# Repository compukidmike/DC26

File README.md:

# DEFCON 26 Projects
This is all the source code and production files for the badges we made for Defcon 26

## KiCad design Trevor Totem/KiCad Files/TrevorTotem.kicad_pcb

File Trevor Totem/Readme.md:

# Trevor Totem
The Trevor Totem was a last minute project for Defcon. It holds 7 SAOs and provides power via 2 AA batteries. It also has LEDs to light up the eyes.

If you're unfamiliar with Trevor the Roach, I suggest watching this video: https://www.youtube.com/watch?v=oOXcol_fFGQ

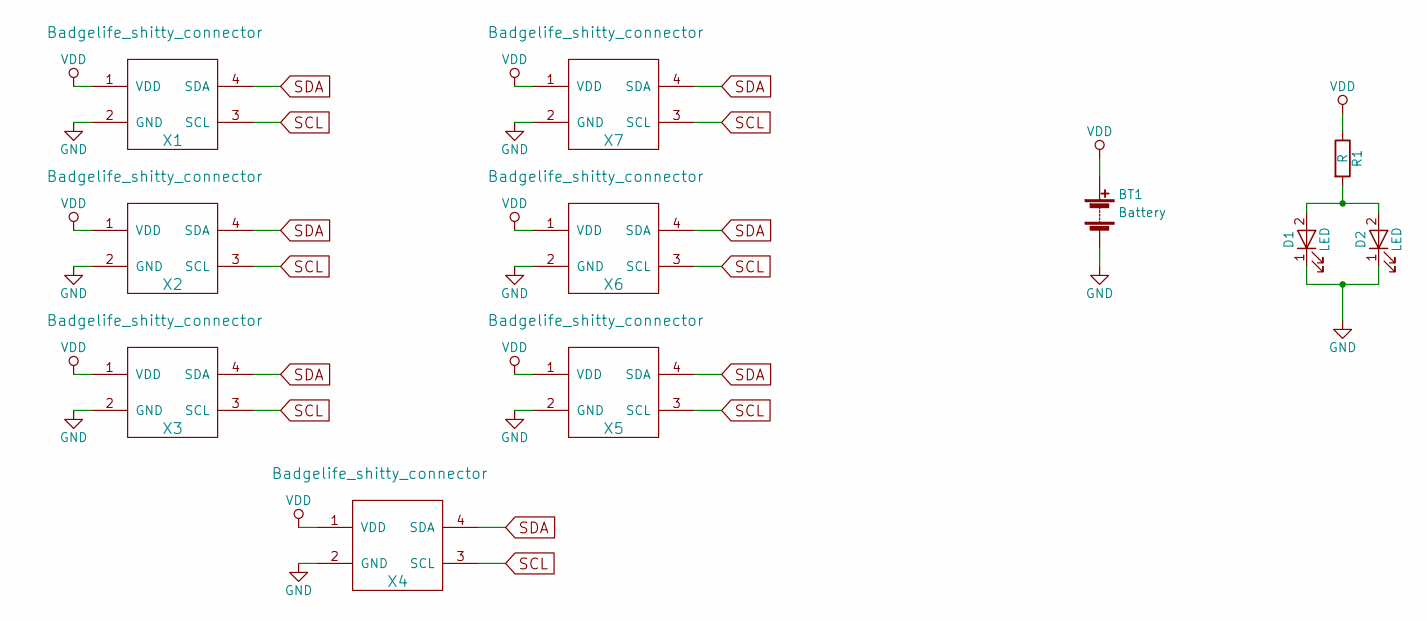
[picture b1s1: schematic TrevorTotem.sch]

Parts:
BT1: Battery; Battery-WireConn
D1, D2: LED; LED-SMD-BottomEntry-OSRAM-LS-T776
R1: R; R_0603_HandSoldering
X1, X2, X3, X4, X5, X6, X7: Badgelife_shitty_connector; Badgelife-Shitty-2x2

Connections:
GND: BT1.2 (-), D1.1 (K), D2.1 (K), X1.2 (GND), X2.2 (GND), X3.2 (GND), X4.2 (GND), X5.2 (GND), X6.2 (GND), X7.2 (GND)
unnamed: D1.2 (A), D2.2 (A), R1.2
SCL: X1.3 (SCL), X2.3 (SCL), X3.3 (SCL), X4.3 (SCL), X5.3 (SCL), X6.3 (SCL), X7.3 (SCL)
SDA: X1.4 (SDA), X2.4 (SDA), X3.4 (SDA), X4.4 (SDA), X5.4 (SDA), X6.4 (SDA), X7.4 (SDA)
VDD: BT1.1 (+), R1.1, X1.1 (VDD), X2.1 (VDD), X3.1 (VDD), X4.1 (VDD), X5.1 (VDD), X6.1 (VDD), X7.1 (VDD)

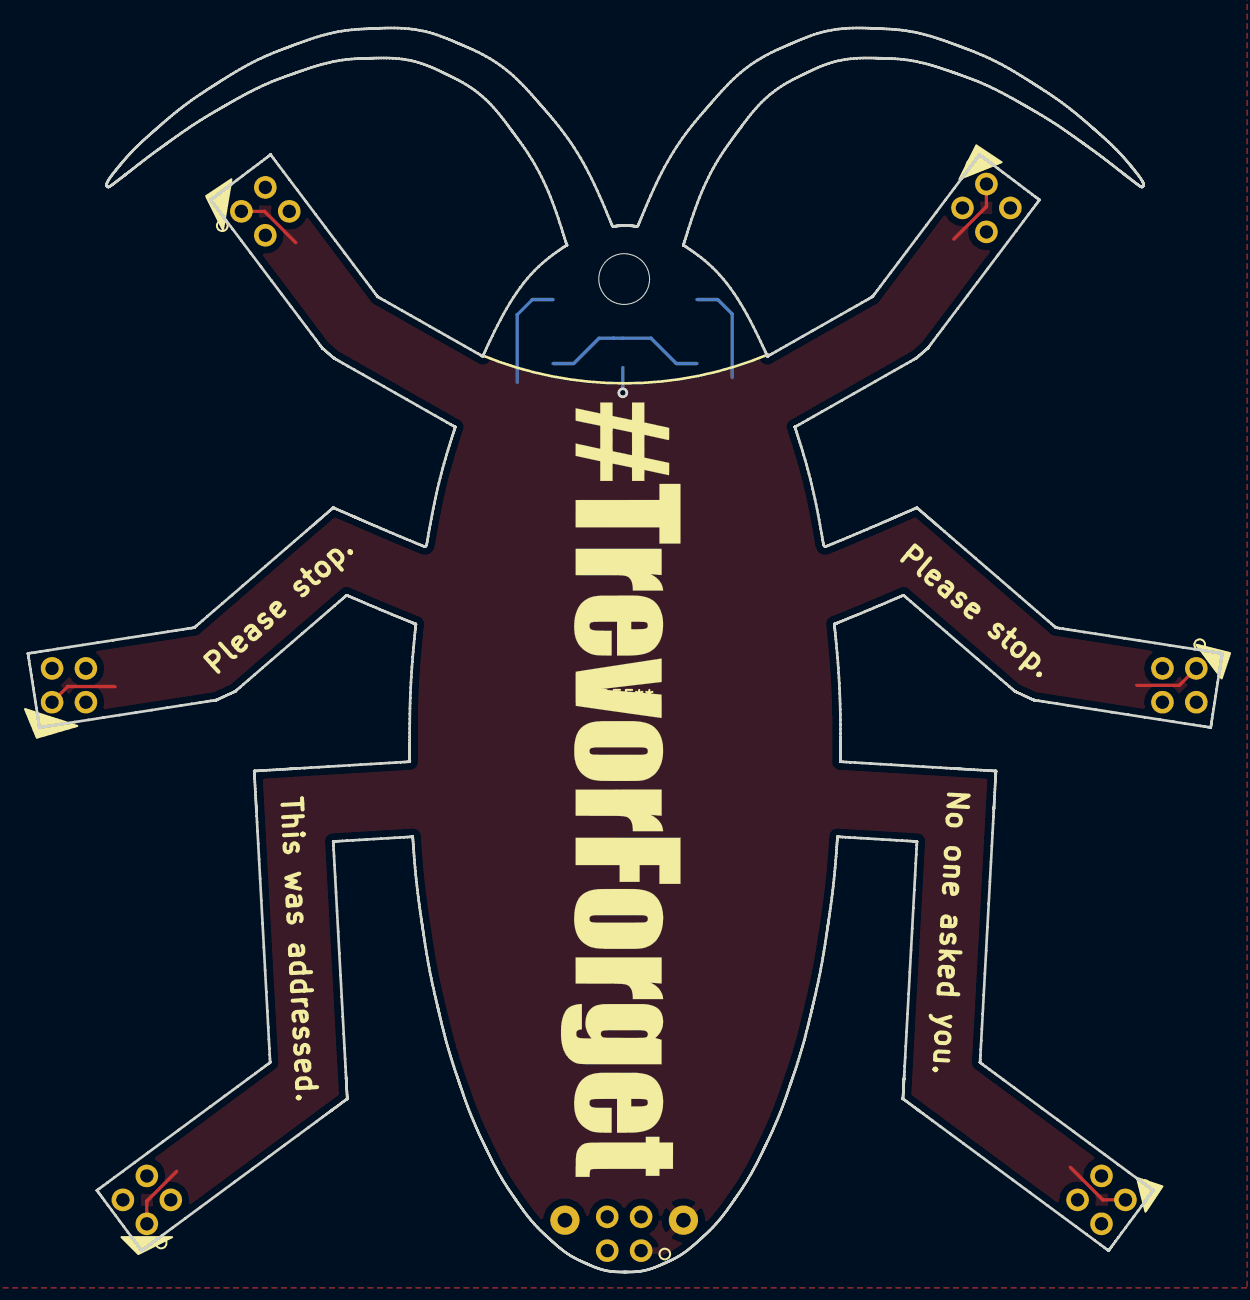
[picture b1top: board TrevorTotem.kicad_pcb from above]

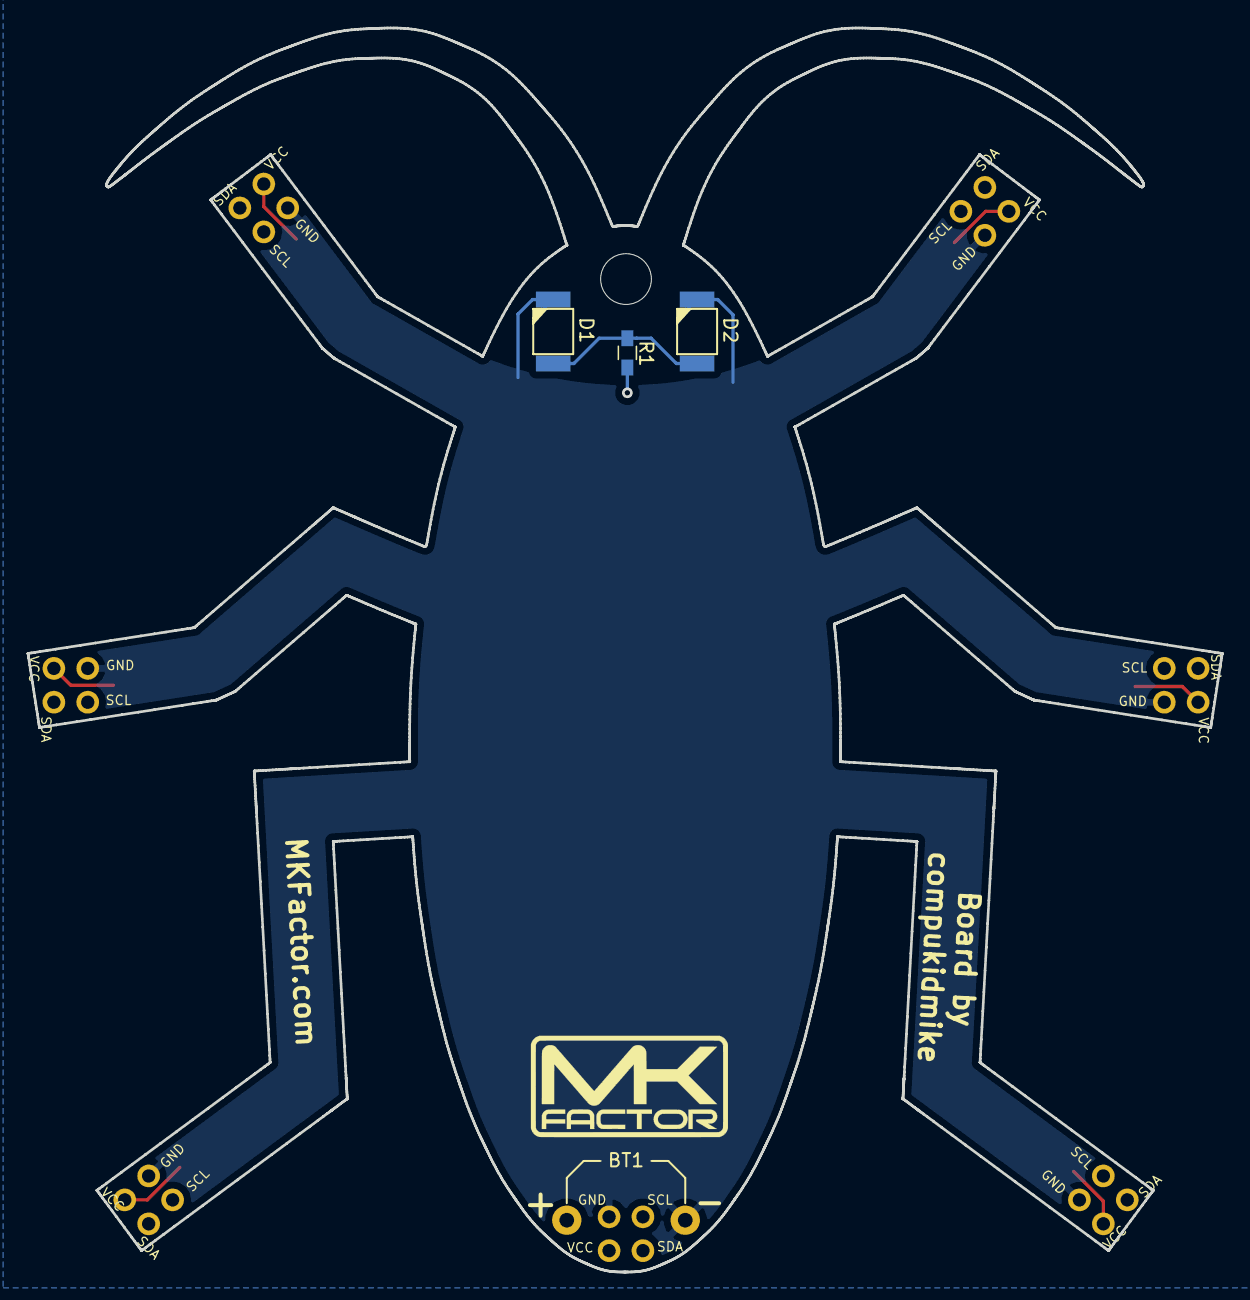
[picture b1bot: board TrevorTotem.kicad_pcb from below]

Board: 2 copper layers, 89.6 x 93.3 mm, 11 parts (4 on the bottom side), 5 nets.

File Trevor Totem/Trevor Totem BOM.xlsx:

Trevor Totem BOM
Part | Qty | Reference | Part Number | Vendor Part Number | Link | Alt Link
4 pin Header Female | 1.0 | X1, X2, X3, X4, X5, X6, X7 | PPTC022LFBN-RC | S7070-ND | https://www.digikey.com/product-detail/en/sullins-connector-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
Resistor LEDs/Transistor 0603 100 | 1.0 | R1 | RMCF0603FG100R | RMCF0603FG100RCT-ND | https://www.digikey.com/product-detail/en/yageo/RC0603JR-071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
LEDs (red) | 2.0 | D1, D2 | LS T776-P2S1-1-Z | 720-LST776-P2S1-1-Z | https://www.digikey.com/product-detail/en/osram-opto-semicon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
Battery Holder | 1.0 | BT1 | 2463.0 | 36-2463-ND | https://www.digikey.com/product-detail/en/keystone-electroni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
PCB 90x94mm | 1.0 |  |  |  | www.allpcb.com

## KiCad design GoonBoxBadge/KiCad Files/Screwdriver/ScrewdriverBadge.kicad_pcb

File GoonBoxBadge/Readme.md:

# GoonBoxBadge
  
This unofficial Defcon badge has been an amazing experience. Thank you to everyone who backed our kickstarter and to those who bought one at Defcon. The response has been amazing.

You will find everything you need to build your own badge here. If I forgot something or you need clarification on something, don't hesitate to reach out.

## Basic Badge Usage
This is the instruction sheet that was in the bag with the badge.  

The most important thing to keep in mind is to not touch the slider or the mode button when turning on the badge. When the badge is first powered on, it goes through a quick calibration of the touch buttons. If you're touching the buttons during this, the calibration will be off and the buttons won't work. If that happens, simply turn the badge off and back on.

The mode button is the top gold ring on the screwdriver, just below the coil. When pressed quickly, it will indicate the current mode on the slider LEDs. If you hold it, it will change modes. Release it when it's on the mode you want (indicated by the slider LEDs, mode 1 is the bottom LEDs). It will remember the last mode, even when turned of.

The screwdriver has 3 modes:
1. Normal mode
    * In this mode the LEDs are off until you touch the slider. The LEDs will light up according to which part of the slider you're touching. The sound will also change frequency based on slider position.
2. Bling mode
    * In this mode the LEDs are always flashing. The speed will change based on the last slider position. The speed of the GoonBox pin LED pulse will also change based on slider position.
3. TV-B-Gone mode
    * This mode is for turning off/on TVs. If you touch the lower parts of the slider, it will transmit codes as long as you're holding it. If you toucht the top of the slider, it will automatically transmit all of the TV codes without you holding it. To cancel, touch the bottom of the slider.
    * Note that the slider is slower to react in this mode. This is due to the TV code transmitting being so timing sensitive. We can't update touch data as quickly as normal during code transmission.
    * After the main badge code, we were only able to fit about half the normal TV-B-Gone codes, so some TVs won't work. However, most of the major brands should be in there.

The GoonBox pin doesn't have any modes, etc.  Simply put in a CR2032 battery and it's ready. It will react to the screwdriver, as well as normal TV remotes.

## Code
The code is very ugly, and I'm sorry for anyone that chooses to look at it. I've sprinkled some comments throughout it, hopefully it makes sense.  
There were issues with the TV-B-Gone functionality. The IR LED was put on a pin that doesn't have hardware PWM functionality. This caused many problems as the standard TV-B-Gone code wouldn't work. I made serious modificaitons to both the code and the IR codes to get it to work.  

## Lessons Learned
  * Test everything you can on the prototypes. Even if you think it might not happen, test it anyway.
  * Assembling 600 badges by hand isn't a great idea. We got it done with time to spare, but still. It's a crazy amount of work/time.
  * Pickup times/locations need to be scheduled far in advance. There were a lot of people that had a hard time finding us or were unable to get to us quickly. We'll do much better about this next year.
  
### Thank you again to everyone who made this project possible!

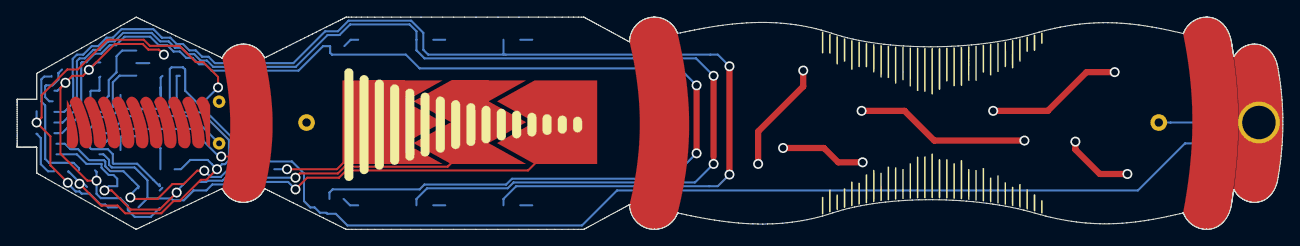
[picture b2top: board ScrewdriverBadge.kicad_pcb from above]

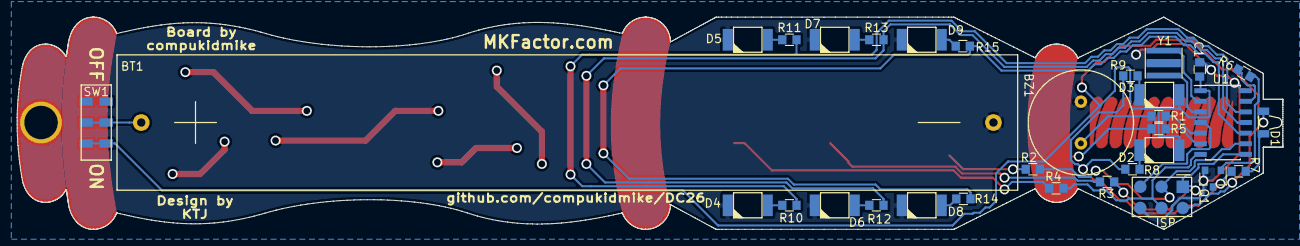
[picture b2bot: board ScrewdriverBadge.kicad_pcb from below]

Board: 2 copper layers, 151.5 x 25.4 mm, 36 parts (32 on the bottom side), 31 nets.

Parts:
BT1: Battery; Battery-2AA-BC12AAPC
BZ1: Buzzer; Buzzer-12.6mm-Murata-PKM13EPYH4000
C1: 0.1uF; R_0603_Mid
D1: LED; LED-IR-RA-OSRAM-SFH-4045N
D2, D3, D4, D5, D6, D7, D8, D9: LED; LED-SMD-BottomEntry-OSRAM-LS-T776
ISP: AVR-ISP-6; ISP-AVR-6Pin-SMD
Q1: BC817; SOT-23
R1, R2, R3, R4, R5, R6, R7, R8, R9, R10, R11, R12, R13, R14, R15: R; R_0603_Mid
SW1: SW_SPST; JS202011JCQN
TP1: SLIDER1; TestPad-SMD-1mm-Tented
TP2: SLIDER2; TestPad-SMD-1mm-Tented
TP3: SLIDER3; TestPad-SMD-1mm-Tented
TP4: FUNC; TestPad-SMD-1mm-Tented
U1: ATTINY84A-SSU; SOIC-14_3.9x8.7mm_Pitch1.27mm
Y1: Resonator; Resonator-AWSCR-3.7x3.1mm

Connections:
+BATT: C1.1, D1.2, D2.2, D3.2, ISP.2, SW1.1, U1.1
BUZZ: R1.2, U1.5
GND: BT1.2, BZ1.2, C1.2, D4.1, D5.1, D6.1, D7.1, D8.1, D9.1, ISP.6, Q1.2, U1.14, Y1.2
IRLED: R6.2, U1.13
LED1: R10.2, R11.2, U1.12
LED2: R12.2, R13.2, U1.11
LED3: R14.2, R15.2, U1.10
MISO: ISP.1, R3.2, U1.8
MOSI: ISP.4, R4.2, U1.7
unnamed: BT1.1, SW1.2
unnamed: BZ1.1, R1.1
unnamed: D1.1, R7.2
unnamed: D2.1, R8.2
unnamed: D3.1, R9.2
unnamed: D4.2, R10.1
unnamed: D5.2, R11.1
unnamed: D6.2, R12.1
unnamed: D7.2, R13.1
unnamed: D8.2, R14.1
unnamed: D9.2, R15.1
unnamed: Q1.1, R6.1
unnamed: Q1.3, R7.1, R8.1, R9.1
unnamed: R2.1, TP1.1
unnamed: R3.1, TP2.1
unnamed: R4.1, TP3.1
unnamed: R5.1, TP4.1
unnamed: R5.2, U1.6
unnamed: U1.2, Y1.3
unnamed: U1.3, Y1.1
RST: ISP.5, U1.4
SCK: ISP.3, R2.2, U1.9

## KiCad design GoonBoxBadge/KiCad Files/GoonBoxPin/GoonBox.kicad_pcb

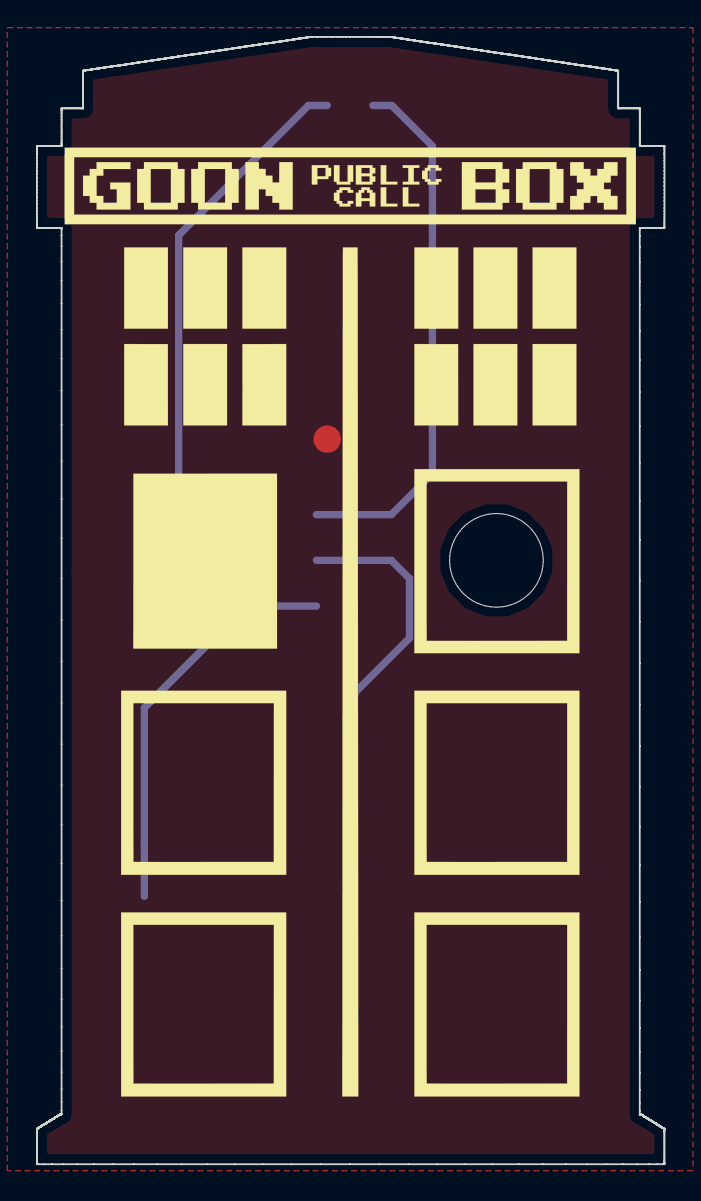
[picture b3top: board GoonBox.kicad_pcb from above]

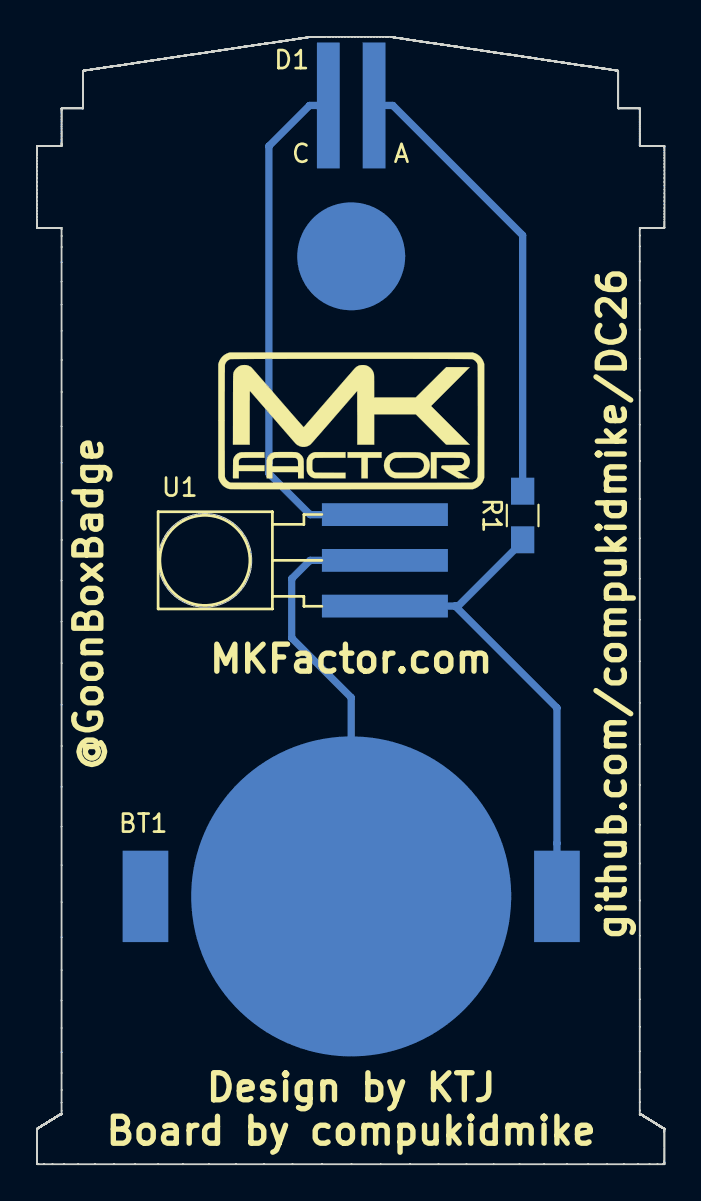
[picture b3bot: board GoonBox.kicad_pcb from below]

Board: 2 copper layers, 34.9 x 62.6 mm, 4 parts (4 on the bottom side), 4 nets.

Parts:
BT1: Battery_Cell; Linx-BAT-HLD-001
D1: LED; LED-5MM-SMT-FLAT
R1: R; R_0805_HandSoldering
U1: TSOP331xx; TSOP332-IR-RCV

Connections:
+BATT: BT1.1, R1.1, U1.3
GND: BT1.2, U1.2
unnamed: D1.1, U1.1
unnamed: D1.2, R1.2

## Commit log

2018-08-13 Add GoonBoxBadge Files
2018-08-13 Add Llama SAO and Trevor Totem files
